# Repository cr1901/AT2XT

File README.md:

# AT-to-XT Keyboard Protocol Converter

This repository provides the source, schematics, and Gerber files that converts
the AT-keyboard protocol to the XT keyboard protocol.

As of 3-22-2026, development has [moved](https://codeberg.org/cr1901/AT2XT) to Codeberg.
Please update your remotes. _This repository is not currently mirrored._

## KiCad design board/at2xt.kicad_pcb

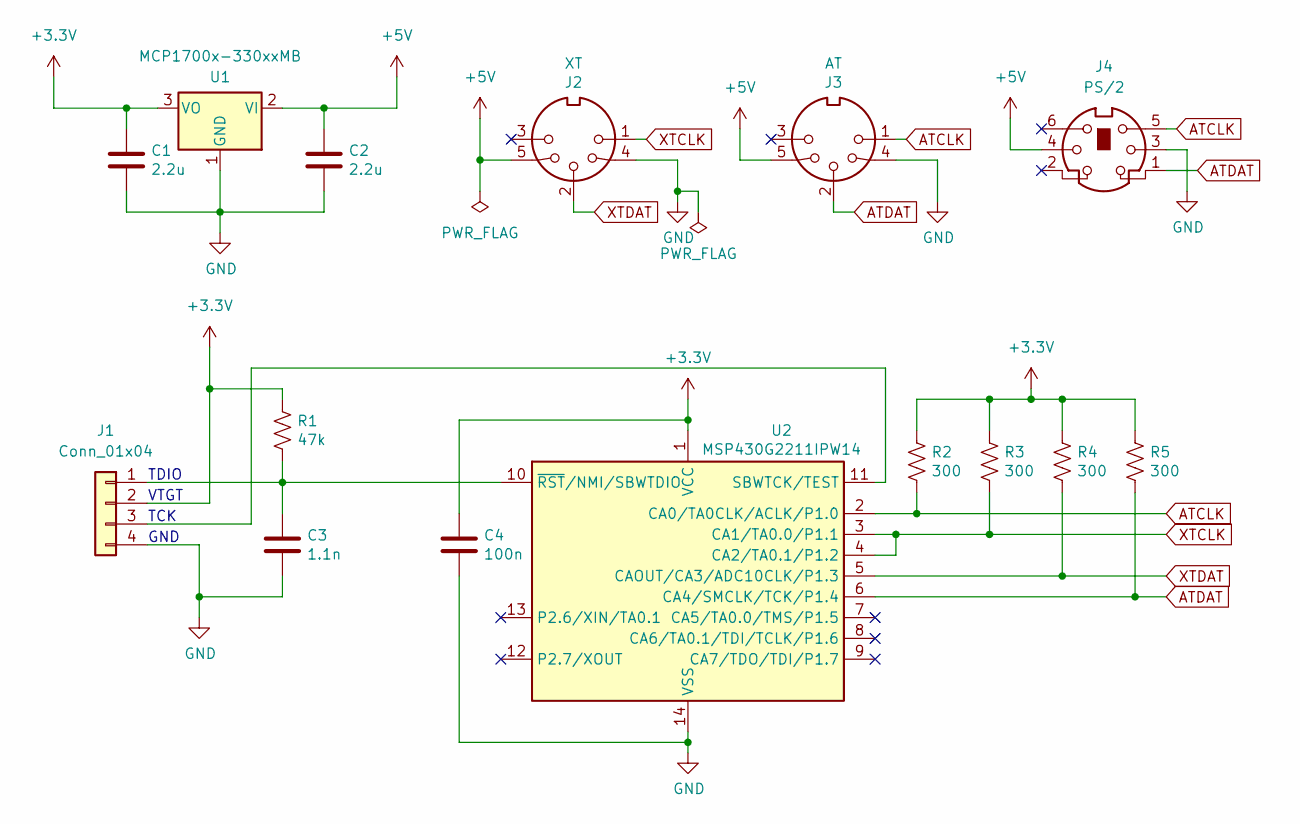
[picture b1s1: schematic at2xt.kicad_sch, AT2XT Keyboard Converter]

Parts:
C1, C2: 2.2u; C_0603_1608Metric; MPN 0603YD225KAT2A
C3: 1.1n; C_0603_1608Metric; MPN 0603YC102KAT2A
C4: 100n; C_0603_1608Metric; MPN 0603YC104KAT2A
J1: Conn_01x04; PinHeader_1x04_P2.54mm_Vertical; MPN TSW-104-14-S-S
J2: XT; DIN41524-5-2MP_20.5mmx15.5mm_P7.5mm_P10.0mm_MP10.0mm; MPN KCDX-5S-N
J3: AT; DIN41524-5-2MP_20.5mmx15.5mm_P7.5mm_P10.0mm_MP10.0mm; MPN KCDX-5S-N
J4: PS/2; MiniDIN-6-3MP_14.0mmx12.9mm_P2.6mm_P6.8mm_MP6.75mm; MPN KMDGX-6S-N
R1: 47k; R_0603_1608Metric; MPN ERJ-3GEYJ473V
R2, R3, R4, R5: 300; R_0603_1608Metric; MPN ERJ-3GEYJ301V
U1: MCP1700x-330xxMB; SOT-89-3; MPN MCP1700T-3302E/MB
U2: MSP430G2211IPW14; TSSOP-14_4.4x5mm_P0.65mm; MPN MSP430G2211IPW14

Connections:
+3.3V: C1.1, C4.1, J1.2, R1.1, R2.1, R3.1, R4.1, R5.1, U1.3 (VO), U2.1 (VCC)
+5V: C2.1, J2.5, J3.5, J4.4, U1.2 (VI)
ATCLK: J3.1, J4.5, R2.2, U2.2 (CA0/TA0CLK/ACLK/P1.0)
ATDAT: J3.2, J4.1, R5.2, U2.6 (CA4/SMCLK/TCK/P1.4)
GND: C1.2, C2.2, C3.2, C4.2, J1.4, J2.4, J3.4, J4.3, U1.1 (GND), U2.14 (VSS)
unnamed: C3.1, J1.1, R1.2, U2.10 (~RST/NMI/SBWTDIO)
unnamed: J1.3, U2.11 (SBWTCK/TEST)
XTCLK: J2.1, R3.2, U2.3 (CA1/TA0.0/P1.1), U2.4 (CA2/TA0.1/P1.2)
XTDAT: J2.2, R4.2, U2.5 (CAOUT/CA3/ADC10CLK/P1.3)

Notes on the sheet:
TDIO
GND
TCK
VTGT

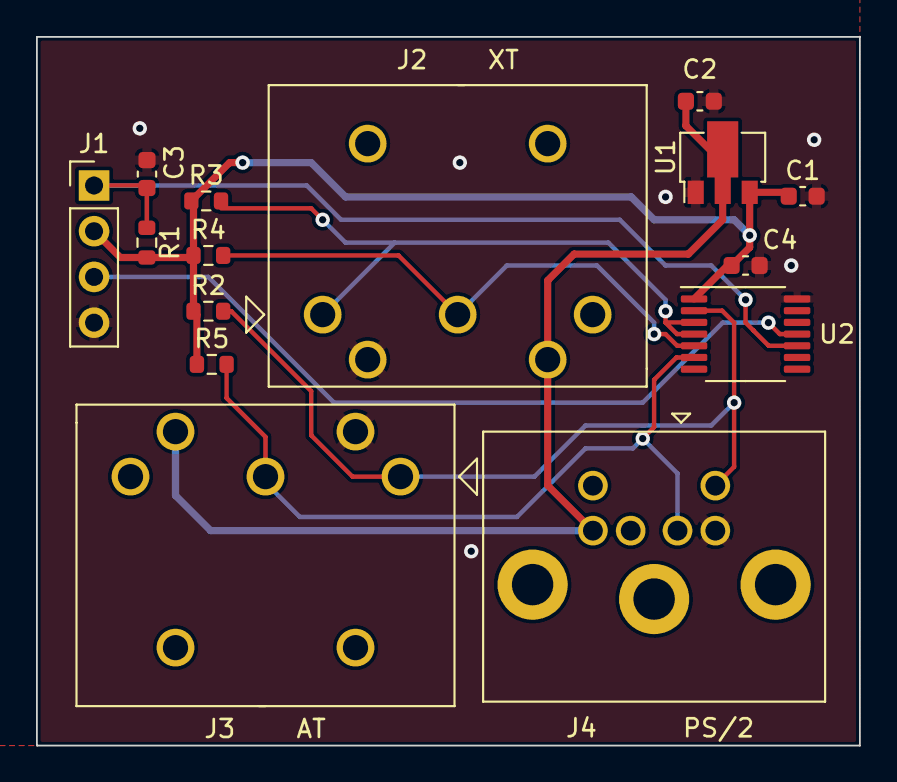
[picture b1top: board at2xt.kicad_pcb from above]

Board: 2 copper layers, 45.7 x 39.4 mm, 15 parts (0 on the bottom side), 9 nets.

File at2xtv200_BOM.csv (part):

"Source:","C:\msys64\home\William\Projects\legacy\AT2XT\board\at2xt.kicad_sch"
"Date:","1/20/2023 1:07:05 PM"
"Tool:","Eeschema (6.0.10)"
"Generator:","C:\Program Files\KiCad\6.0\bin\scripting\plugins/bom_csv_grouped_by_value.py"
"Component Count:","15"

"Individual Components:"

"Item","Qty","Reference(s)","Value","LibPart","Footprint","Datasheet","MFR","MPN","OC_DIGIKEY","OC_MOUSER","URL_DIGIKEY","URL_MOUSER"
"","","C1","2.2u","Device:C","Capacitor_SMD:C_0603_1608Metric","https://datasheets.kyocera-avx.com/X7RDielectric.pdf","Kyocera AVX","0603YD225KAT2A","478-5147-2-ND","581-0603YD225K","https://www.digikey.com/en/products/detail/kyocera-avx/0603Y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","https://www.mouser.com/ProductDetail/KYOCERA-AVX/0603YD225KA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"
"","","C2","2.2u","Device:C","Capacitor_SMD:C_0603_1608Metric","https://datasheets.kyocera-avx.com/X7RDielectric.pdf","Kyocera AVX","0603YD225KAT2A","478-5147-2-ND","581-0603YD225K","https://www.digikey.com/en/products/detail/kyocera-avx/0603Y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","https://www.mouser.com/ProductDetail/KYOCERA-AVX/0603YD225KA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"
"","","C3","1.1n","Device:C","Capacitor_SMD:C_0603_1608Metric","https://datasheets.kyocera-avx.com/X7RDielectric.pdf","Kyocera AVX","06033C112KAT2A","06033C112KAT2A-ND","581-06033C112KAT2A","https://www.digikey.com/en/products/detail/kyocera-avx/06033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","https://www.mouser.com/ProductDetail/KYOCERA-AVX/06033C112KA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"
"","","C4","100n","Device:C","Capacitor_SMD:C_0603_1608Metric","https://datasheets.kyocera-avx.com/X7RDielectric.pdf","Kyocera AVX","0603YC104KAT2A","478-1239-2-ND","581-06035C104KAT2A","https://www.digikey.com/en/products/detail/kyocera-avx/0603Y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","https://www.mouser.com/ProductDetail/KYOCERA-AVX/0603YC104KA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"
"","","J1","Conn_01x04","Connector_Generic:Conn_01x04","Connector_PinHeader_2.54mm:PinHeader_1x04_P2.54mm_Vertical","https://www.mouser.com/datasheet/2/527/tsw_th-2854687.pdf","Samtec","TSW-104-14-S-S","SAM1057-04-ND","200-TSW10414SS","https://www.digikey.com/en/products/detail/samtec-inc/TSW-10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","https://www.mouser.com/ProductDetail/Samtec/TSW-104-14-S-S?q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"
"","","J2","XT","Connector:DIN-5_180degree","at2xt:DIN41524-5-2MP_20.5mmx15.5mm_P7.5mm_P10.0mm_MP10.0mm","https://www.mouser.com/datasheet/2/222/KCDX-334811.pdf","Kycon","KCDX-5S-N","2092-KCDX-5S-N-ND","806-KCDX-5S-N","https://www.digikey.com/en/products/detail/kycon-inc/KCDX-5S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","https://www.mouser.com/ProductDetail/Kycon/KCDX-5S-N?qs=uMQT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"
"","","J3","AT","Connector:DIN-5_180degree","at2xt:DIN41524-5-2MP_20.5mmx15.5mm_P7.5mm_P10.0mm_MP10.0mm","https://www.mouser.com/datasheet/2/222/KCDX-334811.pdf","Kycon","KCDX-5S-N","2092-KCDX-5S-N-ND","806-KCDX-5S-N","https://www.digikey.com/en/products/detail/kycon-inc/KCDX-5S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","https://www.mouser.com/ProductDetail/Kycon/KCDX-5S-N?qs=uMQT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"
"","","J4","PS/2","Connector:Mini-DIN-6","at2xt:MiniDIN-6-3MP_14.0mmx12.9mm_P2.6mm_P6.8mm_MP6.75mm","https://www.kycon.com/2013Catalogpage/Mini-Dins%20%20Circula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","Kycon","KMDGX-6S-N","2092-KMDGX-6S-BS-ND","806-KMDGX-6S-BS","https://www.digikey.com/en/products/detail/kycon-inc/KMDGX-6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","https://www.mouser.com/ProductDetail/Kycon/KMDGX-6S-BS?qs=go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"
"","","R1","47k","Device:R_US","Resistor_SMD:R_0603_1608Metric","https://industrial.panasonic.com/ww/products/pt/general-purp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","Panasonic","ERJ-3GEYJ473V","P47KGTR-ND","667-ERJ-3GEYJ473V","https://www.digikey.com/en/products/detail/panasonic-electro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","https://www.mouser.com/ProductDetail/Panasonic/ERJ-3GEYJ473V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"
"","","R2","300","Device:R_US","Resistor_SMD:R_0603_1608Metric","https://industrial.panasonic.com/ww/products/pt/general-purp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","Panasonic","ERJ-3GEYJ301V ","P300GTR-ND","667-ERJ-3GEYJ301V","https://www.digikey.com/en/products/detail/panasonic-electro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","https://www.mouser.com/ProductDetail/Panasonic/ERJ-3GEYJ301V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"
"","","R3","300","Device:R_US","Resistor_SMD:R_0603_1608Metric","https://industrial.panasonic.com/ww/products/pt/general-purp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","Panasonic","ERJ-3GEYJ301V ","P300GTR-ND","667-ERJ-3GEYJ301V","https://www.digikey.com/en/products/detail/panasonic-electro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","https://www.mouser.com/ProductDetail/Panasonic/ERJ-3GEYJ301V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"
"","","R4","300","Device:R_US","Resistor_SMD:R_0603_1608Metric","https://industrial.panasonic.com/ww/products/pt/general-purp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","Panasonic","ERJ-3GEYJ301V ","P300GTR-ND","667-ERJ-3GEYJ301V","https://www.digikey.com/en/products/detail/panasonic-electro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","https://www.mouser.com/ProductDetail/Panasonic/ERJ-3GEYJ301V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"
"","","R5","300","Device:R_US","Resistor_SMD:R_0603_1608Metric","https://industrial.panasonic.com/ww/products/pt/general-purp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","Panasonic","ERJ-3GEYJ301V ","P300GTR-ND","667-ERJ-3GEYJ301V","https://www.digikey.com/en/products/detail/panasonic-electro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","https://www.mouser.com/ProductDetail/Panasonic/ERJ-3GEYJ301V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"
"","","U1","MCP1700x-330xxMB","Regulator_Linear:MCP1700x-330xxMB","Package_TO_SOT_SMD:SOT-89-3","http://ww1.microchip.com/downloads/en/DeviceDoc/20001826D.pdf","Microchip","MCP1700T-3302E/MB","MCP1700T3302EMBTR-ND","579-MCP1700T3302E/MB","https://www.digikey.com/en/products/detail/microchip-technol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","https://www.mouser.com/ProductDetail/Microchip-Technology-At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"
"","","U2","MSP430G2211IPW14","MCU_Texas_MSP430:MSP430G2211IPW14","Package_SO:TSSOP-14_4.4x5mm_P0.65mm","http://www.ti.com/lit/ds/symlink/msp430g2211.pdf","Texas Instruments","MSP430G2211IPW14","296-25830-5-ND","595-MSP430G2211IPW14 ","https://www.digikey.com/en/products/detail/texas-instruments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","https://www.mouser.com/ProductDetail/Texas-Instruments/MSP43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"



"Collated Components:"

"Item","Qty","Reference(s)","Value","LibPart","Footprint","Datasheet","MFR","MPN","OC_DIGIKEY","OC_MOUSER","URL_DIGIKEY","URL_MOUSER"
"1","2","C1, C2","2.2u","Device:C","Capacitor_SMD:C_0603_1608Metric","https://datasheets.kyocera-avx.com/X7RDielectric.pdf","Kyocera AVX","0603YD225KAT2A","478-5147-2-ND","581-0603YD225K","https://www.digikey.com/en/products/detail/kyocera-avx/0603Y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","https://www.mouser.com/ProductDetail/KYOCERA-AVX/0603YD225KA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"
"2","1","C3","1.1n","Device:C","Capacitor_SMD:C_0603_1608Metric","https://datasheets.kyocera-avx.com/X7RDielectric.pdf","Kyocera AVX","06033C112KAT2A","06033C112KAT2A-ND","581-06033C112KAT2A","https://www.digikey.com/en/products/detail/kyocera-avx/06033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","https://www.mouser.com/ProductDetail/KYOCERA-AVX/06033C112KA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"
"3","1","C4","100n","Device:C","Capacitor_SMD:C_0603_1608Metric","https://datasheets.kyocera-avx.com/X7RDielectric.pdf","Kyocera AVX","0603YC104KAT2A","478-1239-2-ND","581-06035C104KAT2A","https://www.digikey.com/en/products/detail/kyocera-avx/0603Y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","https://www.mouser.com/ProductDetail/KYOCERA-AVX/0603YC104KA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"
"4","1","J1","Conn_01x04","Connector_Generic:Conn_01x04","Connector_PinHeader_2.54mm:PinHeader_1x04_P2.54mm_Vertical","https://www.mouser.com/datasheet/2/527/tsw_th-2854687.pdf","Samtec","TSW-104-14-S-S","SAM1057-04-ND","200-TSW10414SS","https://www.digikey.com/en/products/detail/samtec-inc/TSW-10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","https://www.mouser.com/ProductDetail/Samtec/TSW-104-14-S-S?q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"
"5","1","J2","XT","Connector:DIN-5_180degree","at2xt:DIN41524-5-2MP_20.5mmx15.5mm_P7.5mm_P10.0mm_MP10.0mm","https://www.mouser.com/datasheet/2/222/KCDX-334811.pdf","Kycon","KCDX-5S-N","2092-KCDX-5S-N-ND","806-KCDX-5S-N","https://www.digikey.com/en/products/detail/kycon-inc/KCDX-5S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","https://www.mouser.com/ProductDetail/Kycon/KCDX-5S-N?qs=uMQT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"
"6","1","J3","AT","Connector:DIN-5_180degree","at2xt:DIN41524-5-2MP_20.5mmx15.5mm_P7.5mm_P10.0mm_MP10.0mm","https://www.mouser.com/datasheet/2/222/KCDX-334811.pdf","Kycon","KCDX-5S-N","2092-KCDX-5S-N-ND","806-KCDX-5S-N","https://www.digikey.com/en/products/detail/kycon-inc/KCDX-5S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","https://www.mouser.com/ProductDetail/Kycon/KCDX-5S-N?qs=uMQT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"
"7","1","J4","PS/2","Connector:Mini-DIN-6","at2xt:MiniDIN-6-3MP_14.0mmx12.9mm_P2.6mm_P6.8mm_MP6.75mm","https://www.kycon.com/2013Catalogpage/Mini-Dins%20%20Circula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","Kycon","KMDGX-6S-N","2092-KMDGX-6S-BS-ND","806-KMDGX-6S-BS","https://www.digikey.com/en/products/detail/kycon-inc/KMDGX-6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","https://www.mouser.com/ProductDetail/Kycon/KMDGX-6S-BS?qs=go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"
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
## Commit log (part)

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2015-03-29 Initial commit.
2015-03-29 Remove redundant bottom silk gerber file, fix bad top silk
2017-06-13 Move C files to legacy directory.
2017-06-14 Add keyboard pin GPIO driver to move out I/O accesses from main
2017-06-17 Move some regs out of main, add interrupt helper module
2017-06-17 Add utility function file
2017-06-18 Add KeyIn buffer for convenience
2017-06-18 Start interrupt fn. Add inhibit/idle for at side
2017-06-19 Manually checked raw ptr access will have to do for now
2017-06-19 Buffers are now safe
2017-06-19 Fix int asm to deal w/ MSP430 errata.
2017-06-20 Break out critical_section code to require user to manually invoke.
2017-06-22 Add KeyOut buffer due to erroneous assumption
2017-06-22 Add host mode (unsafe!), first draft for testing purposes
2017-06-26 Reading SR should be volatile to prevent reordering with disable().
2017-07-02 Shifting in should OR with contents not AND
2017-07-02 Fix race condition in checking empty buffer (KeyIn/KeyOut should be okay, as msp430 CMP should be atomic)
2017-07-10 Fix incorrect comparison on check for full buffer.
2017-07-11 Minor formatting tweaks. All I/O drivers functional.
2017-07-11 Add FSM logic (does not compile due to missing multiplication).
2017-07-11 Link against software multiplier routines.
2017-07-12 Dummy commit to test panicking
2017-07-12 panicking was optimized out by LLVM- fix
2017-07-12 Fix initialization error due to lack of .bss zeroing- exposed by working panic impl
2017-07-12 Add E0 handling for remaining keycodes except Pause.
2017-07-12 Add pause handling w/ Num Lock guard (Scroll Lock glitch w/ Ctrl + Pause). Firmware fully functional.
2017-07-12 Clean code to remove warnings/follow conventions.
2017-07-12 Remove util.rs because I'm a bad person apparently if I keep it: https://twitter.com/withoutboats/status/877761222073925633 Bump version.
2017-07-12 Use mutexes for global booleans.
2017-07-15 Add .data initialization support (mutexes need it). Still buggy.
2017-07-15 Remove Result<> from FSM. Actually increases space./compare.sh at2xt-good2.lst at2xt-bad2.lst mutex.diff Dummy commit.
2017-07-15 Use zero_bss instead of calling clear fcns for each global.
2017-07-15 Make accesses to KEY_OUT safe. Remove critical section; make Mutex's responsibility to avoid data race (or opt into unsafety).
2017-07-16 IN_BUFFER is safe, but code doesn't fit on -O3.
2017-07-16 Start grafting msp430-rt onto this project (does not compile).
2017-07-16 Still linking against libc for memcpy/memset, no need for compiler_builtins mem. Update msp430.json; recent (within the month) nightly crashes w/ the old version, and fixes ABI error.
2017-07-16 Provide memcpy/memset from compiler_builtins.
2017-07-16 Replace msp430-rt and manual interrupt handling with msp430g2211.
2017-07-16 Use msp430g2211 API in keyboard pin driver. Linker symbols no longer required.
2017-07-16 Remove peripheral linker symbols provided by TI- no longer needed to link.
2017-07-16 Add more information on prerequisites and schematic.
2017-07-17 Gain approx 70 bytes back from opting into controlled (i.e. still safe) unsafety.
2017-07-17 Optimize based on observation that some areas have ints disabled already and don't touch global vars belonging to other ints.
2017-07-17 Swap keyboard driver to take PORT_1_2 peripheral directly. Ensure it compiles by commenting out relevant main code.
2017-07-17 Implement remaining functions. RTFM firmware compiles completely.
2017-07-17 Clean up unused imports. free -> rtfm::atomic. Bump to version 2.0.0 b/c of structural change.
2017-07-18 BitwiseReverse uses less space and performance drop is negligible
2017-07-23 Use msp430_atomic::AtomicBool to avoid critical sections
2017-07-23 Pin versions in Cargo.toml before continuing (compile errors on clean build). r0 dependency replace is ignored.
2017-07-23 RTFM syntax changes. msp430-rt now on crates.io.
2017-07-23 Tick count was wrong for not(use-timer) delays. Add Makefile target for timer.
2017-07-24 Timer never fired in the first place- enable interrupt.
2017-07-24 Increase LED toggle delay so firmware doesn't start sending next byte while recieving ack from keyboard.
2017-07-24 TIMEOUT is safe as AtomicBool. 16 byte savings.
2017-07-30 Pin RTFM to before-stable version due to code generation problems.
2017-07-30 Add long-needed and fully-populated CHANGELOG.md
2018-01-29 Bring dependencies up to date, add new compiler flags for thinLTO changes, add stub abort() which is now required (move it later). Does not compile due to overflow.
2018-01-29 First attempt at travis.yml
2018-01-29 Add .travis.yml. Add new workaround for gcc 6.4.0.
2018-01-29 Add TravisCI badge, disable caching for now to simulate completely clean builds as per README.md instructions.
2018-01-29 Add "Dependencies Caveats" section to README.md to sum up maintenance work after a 6 month absence.
2018-02-02 Update dependencies for newly-published msp430-rt with Termination trait.
2018-02-21 Get full symbol name outputs for debugging purposes.
2018-04-21 TI direct link to msp430-gcc returns 403 Forbidden; point to my copy instead.
2018-05-07 Update msp430g2211 version to fix the build on recent nightlies.
2018-06-11 Update README.md
    Link to the document from Microsoft I used to get XT extended keycodes finally.
2018-10-31 Feature gate proc_macro_gen no longer needed.
2018-10-31 Feature gate proc_macro_gen and feature proc_macro no longer needed. (#6)
    proc_macro was stabilized in Rust 1.29. See [1] for relevant commit.
    [1] https://github.com/rust-lang/rust/commit/65f3007fa8a08daf77f2b8382a56eb80cb277131
2018-11-18 Cleanup driver.rs, provide our own panic_handler- msp430-rt's is outdated.
2018-11-18 Bump version to 2.2.0. Update CHANGELOG.md.
2019-09-09 Annotate dependency overrides, remove panic_handler and use panic_msp430.
2019-09-09 const_fn is a standard feature- remove.
2020-01-02 Simplify Cargo profiles and rustflags.
2020-01-13 Update CHANGELOG.md, fix warnings. Tag v2.3.0.
2020-01-15 Fix so that v1.3.0 compiles with recent nightlies (for comparison purposes).
2020-01-15 Import timer feature.
2020-01-15 Translate AT2XT from borrow API to take API- first (naive) pass.
2020-01-15 Remove unnecessary critical section.
2020-01-15 Add missing cfg feature gates.
2020-01-15 Fix typo when porting that caused AT keyboard communication to fail.
2020-03-04 Test CriticalSection optimization in upstream msp430-rt.
2020-03-04 Add extra targets to Justfile.
2020-03-05 Slightly change keymap behavior to get 10 bytes savings.
2020-03-07 Bring README.md more up to date.
2020-03-07 Add legacy Makefile for C code (finally).
2020-03-07 KeyCodeBuffer::put() now returns Result and checks for overflow: 16 bytes added.
2020-03-07 Combine CriticalSections in while loops for 42 bytes savings!
2020-03-07 Convert XT functions to use Result types; requires 46 bytes.
2020-03-07 Convert AT function to use Result return type; requires 64 bytes.
2020-03-07 Remove timer feature- using the timer is now default; there are few space optimizations left to get closer to software-delay size.
2020-03-15 Remove LLVM misoptimization workaround. Fixes #1.
2020-03-15 Remove outdated comments in preparation for refactor.
2020-03-15 Clean up unneeded attributes (and suppress unused_unsafe warning).
2020-03-15 Add support for xargo fix (and run it).
2020-03-15 xargo fix w/ clippy.
2020-03-15 Re-add unwrap which seems to be optimized properly now.
2020-03-15 Refine clippy targets in Justfile.
2020-03-15 Add xargo fmt to Justfile and run.
2020-03-15 Fix as-conversions where possible.
2020-03-16 Justfile modifications.
2020-03-16 Use lints to remove array indexing with zero-cost.
2020-03-16 Add one final lint for now/fix.
2020-03-16 Revert "Add clippy to Travis CI." Potential for lots of breakage.
    This reverts commit 6ba9687003e9ecaafec56ee397f87051f15d4b69.
2020-03-16 Uppercase globals.
2020-03-16 Replace driver macros with generics. No changes in binary.
2020-03-20 Clean up generics + xargo fmt.
2020-03-20 Convert LED mask to dedicated bitflag type.
2020-03-20 Convert most literals to constant items.
2020-03-22 Refactor idle optimization.
2020-03-22 Further refactor
2020-03-23 Optimize expecting_pause check. This may in fact optimize away setting the variable!
2020-03-23 Move peripheral access struct and helpers to own module.
2020-04-04 Simplify match statements on Option/Result to use methods instead.
2020-04-04 Create periph_ref_map to replace public periph_ref.
2020-04-04 Fix version in Cargo.toml. Tag v4.0.0.
2020-04-04 Fix double-reference oversight on periph_ref_map, embed map conversion.
2020-04-04 Add original XTATKEY source to tree under legacy-src.
2020-04-04 Add internal _diff-asm target to Justfile.
2020-04-22 Contrain set/clear_port_reg implementations to prevent UB in safe code.
2020-04-23 Conclude that enable_at_clk_int is safe- already used in safe code, and all shared accesses require interrupts disabled globally.
2020-04-24 Use upstream msp430g2211 crate to remove unsafe writes that are known to be safe. Add deny(unsafe_code).
2020-05-04 Use cargo's unstable build-std feature instead of Xargo. Bring README.md up to date.
2020-06-04 Update Cargo.toml
    Use branch of msp430-atomic with llvm_asm! macro.
2020-09-01 Link in interrupt vectors properly in legacy C code.
2020-09-02 Make an attempt to get the old C firmware to compile with Clang.
2020-09-02 Unify gcc and clang Makefiles, add target to copy build artifacts to subdirectory.
2020-09-02 Force .data and .bss init code to be linked in. __mspabi_func_epilogs now present in clang output.
2020-09-20 Point to v0.1.2 of msp430_atomic with llvm_asm! macro, remove rlibc dependency, as build-std now provides the symbols.
2020-09-20 Emit llvm IR as well in timer-extra.
2020-09-20 Rework Justfile flags passed to commands.
2021-02-24 Attempt to migrate CI to GHA.
2021-02-24 Download msp430 toolchain using GHA.
2021-02-24 Use -nv flag for wget to disable progress bar output in GHA.
2021-02-24 Add cron build to GHA to track nightly compiler.
2021-02-24 Remove redundant semicolon to quash warning.
2021-02-24 Fix some simple clippy warnings.
2021-03-04 Attempt to cache the msp430-gcc toolchain during CI builds.
2021-04-16 msp430g2211 v0.2.1 published to crates.io.
2021-10-19 Remove outdated comment re: enable_at_clk_int unsafety, replace with a comment on how it can be misused safely.
2022-01-26 Update CHANGELOG.md and Cargo.toml. Tag v4.1.0.
2022-01-28 Update to crates.io version of msp430-atomic.
2022-01-28 Clean up pin driver implementation.
2022-05-21 Add rust-toolchain.toml and modify .cargo/config so "cargo build --release" works.
2022-08-18 Set dotenv-load in Justfile, emit assembly from rustc.
2022-11-08 Remove dependency on bare-metal.
2022-11-08 Offset size increase by fixing errant unwrap.
2022-11-30 Convert keybuffer to lock-free implementation; not tested, RefCell not removed.
2022-11-30 Rework IN_BUFFER management in idle loop.
2022-11-30 Convert periph_ref to consume CriticalSection tokens.
2023-01-16 Add Kicad schematic and fully-routed board (finally!). Subject to change.
2023-01-16 Apply some more suggestions from dragonmux's hoard.
2023-01-16 Add .gitattributes for board folder, add name/version to silkscreen.
2023-01-16 Remove old DipTrace ASCII schematic, not needed anymore.
2023-01-18 Annotate parts, regenerate PCB, gerbers, and drill file.
2023-01-18 Minor silkscreen fixups, swap out regulator for part readily available from Mouser.
2023-01-18 Fix errant value for regulator (wrong identifier, correct package).
2023-01-18 Update BOM with correct regulator package.
2023-01-18 Fixed OC_MOUSER for one of the capacitors.
2023-01-30 Use calibration data to derive 1.6MHz+ clock. Comment init function better. cargo fmt.
2023-01-31 Bring building firmware instructions up to date.
2023-02-01 Rearrange the rest of README.md and bring up to date.
2023-02-08 Add support for adding version info to msp430g2211 Information Memory.
2023-12-22 Add renovate.json
2023-12-22 Update actions/cache action to v3
2023-12-22 Update actions/checkout action to v4
2023-12-22 Update all dependencies
2023-12-22 Update renovate.json
    Remove trailing comma, which violates JSON spec.
2023-12-22 Delete .github/dependabot.yml
    Dependabot requires a Cargo.lock, which at present I don't want to provide. Use renovate as an alternative.
2024-03-12 Update extractions/setup-just action to v2
